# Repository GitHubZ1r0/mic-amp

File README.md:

# Microphone amplifier for Knowles Electret microphones

## Overview
This printed circuit board (PCB) is based on the design created at Eaton
Peabody Laboratories (Mass. Eye and Ear Infirmary), but redesigned to work at
lower frequencies. It features:

* High-pass input filter with 96 Hz cutoff.
* Selectable 20 or 40 dB gain
* Low-pass amplification with a 72 kHz cutoff.
* Low-noise 1.5V supply for microphone with a low-pass filter cutoff of 0.33 Hz
  (ensuring that very little noise makes it into the microphone).

The board is 74mm x 48mm and the mounting holes, spaced 40mm x 40mm, are sized
for a M3 screw. The board will fit in a Hammond enclosure that accomodates 75mm
wide boards.

## Getting started
OSH Park will print and ship three of these boards for approximately $30. 

Order the parts from the [bill of materials](part%20list.md).

Solder the parts using solder with water-soluble flux.

Wash the board with dH<sub>2</sub>O.

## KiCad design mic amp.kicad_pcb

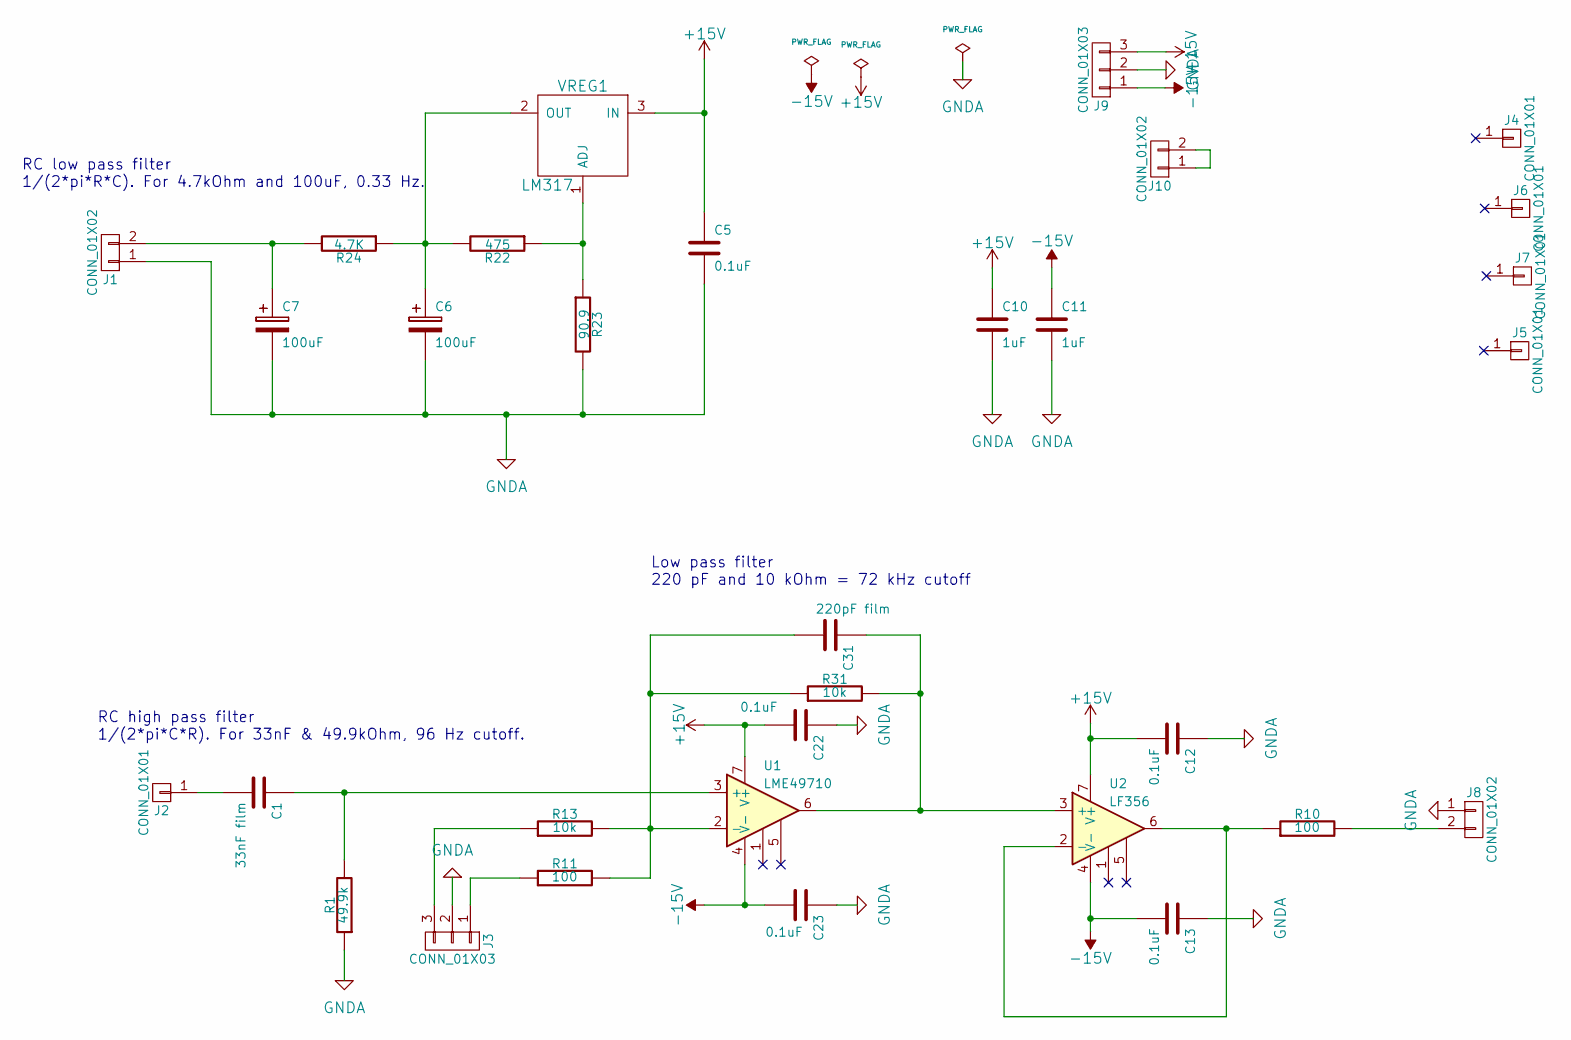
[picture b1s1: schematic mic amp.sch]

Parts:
C1: 33nF film; C_Rect_L7.2mm_W8.5mm_P5.00mm_FKP2_FKP2_MKS2_MKP2
C5, C12, C13, C22, C23: 0.1uF; C_Rect_L4.0mm_W3.5mm_P2.50mm
C6, C7: 100uF; CP_Radial_D10.0mm_P5.00mm
C10, C11: 1uF; C_Rect_L5.5mm_W4.0mm_P2.50mm
C31: 220pF film; C_Rect_L7.2mm_W4.5mm_P5.00mm_FKS2_FKP2_MKS2_MKP2
J1, J8, J10: CONN_01X02; PinSocket_1x02_P2.54mm_Vertical
J2: CONN_01X01; PinSocket_1x01_P2.54mm_Vertical
J3, J9: CONN_01X03; PinSocket_1x03_P2.54mm_Vertical
J4, J5, J6, J7: CONN_01X01; MountingHole_3.2mm_M3
R1: 49.9k; R_Axial_DIN0207_L6.3mm_D2.5mm_P7.62mm_Horizontal
R10, R11: 100; R_Axial_DIN0207_L6.3mm_D2.5mm_P7.62mm_Horizontal
R13, R31: 10k; R_Axial_DIN0207_L6.3mm_D2.5mm_P7.62mm_Horizontal
R22: 475; R_Axial_DIN0207_L6.3mm_D2.5mm_P7.62mm_Horizontal
R23: 90.9; R_Axial_DIN0207_L6.3mm_D2.5mm_P7.62mm_Horizontal
R24: 4.7K; R_Axial_DIN0207_L6.3mm_D2.5mm_P7.62mm_Horizontal
U1: LME49710; DIP-8_W7.62mm_LongPads
U2: LF356; DIP-8_W7.62mm_LongPads
VREG1: LM317; TO-92_Inline_Wide

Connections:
+15V: C5.1, C10.1, C12.2, C22.2, J9.3, U1.7 (V+), U2.7 (V+), VREG1.3 (IN)
-15V: C11.1, C13.2, C23.2, J9.1, U1.4 (V-), U2.4 (V-)
GNDA: C5.2, C6.2, C7.2, C10.2, C11.2, C12.1, C13.1, C22.1, C23.1, J1.1, J3.2, J8.1, J9.2, R1.1, R23.2
unnamed: C1.1, R1.2, U1.3 (+)
unnamed: C1.2, J2.1
unnamed: C6.1, R22.2, R24.1, VREG1.2 (OUT)
unnamed: C7.1, J1.2, R24.2
unnamed: C31.1, R31.2, U1.6, U2.3 (+)
unnamed: C31.2, R11.2, R13.2, R31.1, U1.2 (-)
unnamed: J3.1, R11.1
unnamed: J3.3, R13.1
unnamed: J8.2, R10.2
unnamed: J10.1, J10.2
unnamed: R10.1, U2.2 (-), U2.6
unnamed: R22.1, R23.1, VREG1.1 (ADJ)

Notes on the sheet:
RC high pass filter 1/(2*pi*C*R). For 33nF & 49.9kOhm, 96 Hz cutoff.
RC low pass filter 1/(2*pi*R*C). For 4.7kOhm and 100uF, 0.33 Hz.
Low pass filter 220 pF and 10 kOhm = 72 kHz cutoff

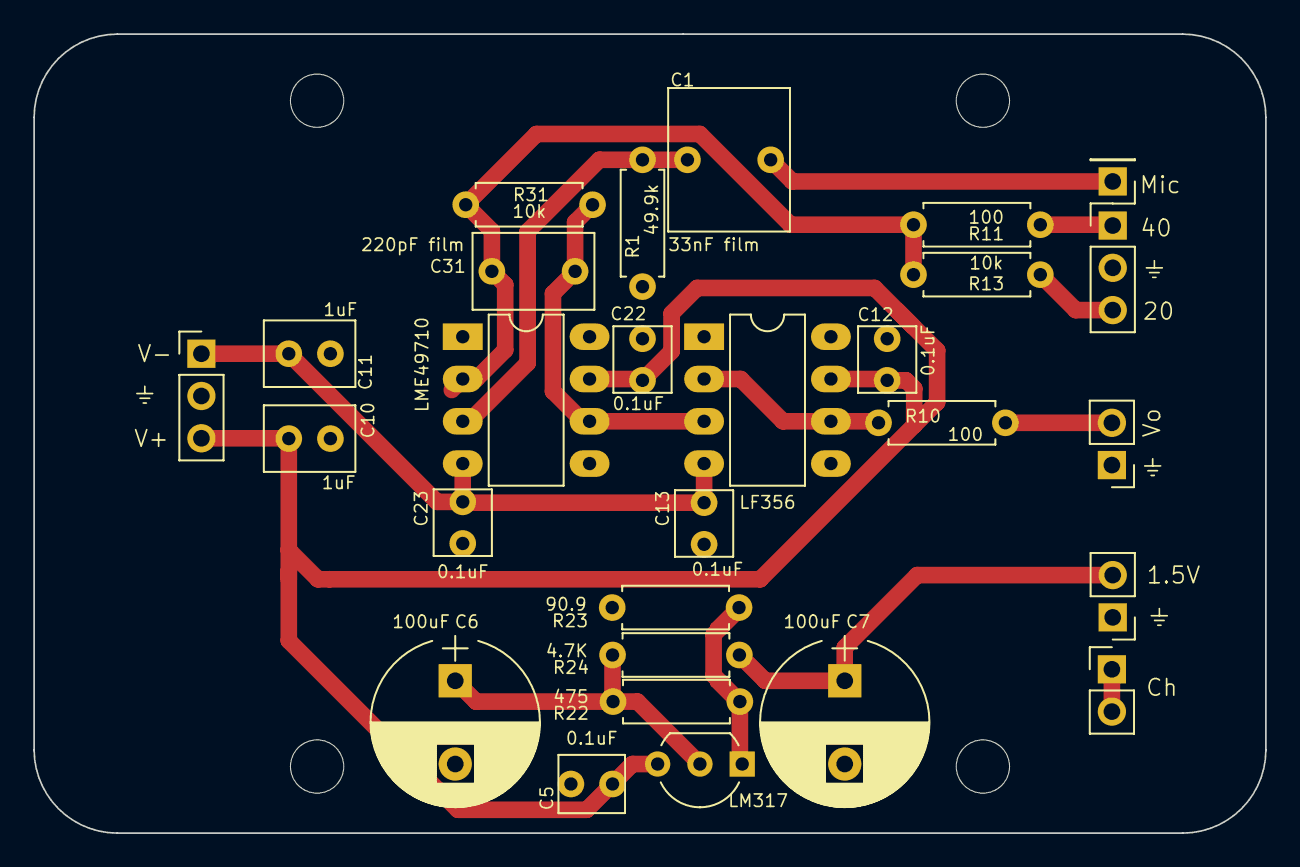
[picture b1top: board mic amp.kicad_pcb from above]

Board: 2 copper layers, 74.0 x 48.0 mm, 32 parts (0 on the bottom side), 15 nets.

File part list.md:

| References             | Number | Value      | Part number        | Note                                                   |
| ---------------------- | ------ | ---------- | ------------------ | ------------------------------------------------------ |
| C1                     | 1      | 33nF       | FKP2C023301L00HI00 | use metal film                                         |
| C5, C12, C13, C22, C23 | 5      | 0.1uF      | RDER72A104K1S1H03A |                                                        |
| C6, C7                 | 2      | 100uF      | UKL1V101KPDANA     |                                                        |
| C10, C11               | 2      | 1uF        | RDER72A105K2P1H03B |                                                        |
| C31                    | 1      | 220pF      | FKP2D002201D00HSSD | use metal film                                         |
| J1, J8, J10            | 3      | CONN_01X02 |                    |                                                        |
| J2                     | 1      | CONN_01X01 |                    |                                                        |
| J3, J9                 | 2      | CONN_01X03 |                    |                                                        |
| J4, J5, J6, J7         | 4      | CONN_01X01 |                    |                                                        |
| R1                     | 1      | 49.9k      | YR1B49K9CC         |                                                        |
| R10, R11               | 2      | 100        | YR1B100RCC         |                                                        |
| R13                    | 1      | 1k         | YR1B1K0CC          |                                                        |
| R22                    | 1      | 475        | YR1B499RCC         |                                                        |
| R23                    | 1      | 90.9       | YR1B90R9CC         |                                                        |
| R24                    | 1      | 4.7K       | YR1B4K75CC         |                                                        |
| R31                    | 1      | 10k        | YR1B10KCC          |                                                        |
| U1                     | 1      | LME49710   | LME49710NA/NOPB    | this part is end-of-life, order extra if you need more |
| U2                     | 1      | LF356      | LF356N/NOPB        |                                                        |
| VREG1                  | 1      | LM317      | LM317LZ/NOPB       |                                                        |

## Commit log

2015-11-20 Commit before major revisions
2017-11-29 ENH: Updated through-hole version
2017-11-29 Remove backup file
2017-11-29 Add gerber files and gitignore
2017-12-19 Through-hole version of mic amp
    Printed via OSH park. Part list availbale via Mouser (see 171218 mic amp
    project). Designed to fit a Hammond enclosure that accomodates 75mm wide
    PCBs.
2017-12-20 Update readme and added parts list and PCB image
2017-12-20 Update parts list, fix circuit board image
2017-12-20 Fixes to the readme
2017-12-20 Fix filename reference for image in readme
2017-12-20 Finally got image to render in readme
